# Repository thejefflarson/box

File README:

+-----------+
|           |
|   . . .   |
|   . . .   |
|   . . .   |
|           |
+-----------+

LED box for my son!

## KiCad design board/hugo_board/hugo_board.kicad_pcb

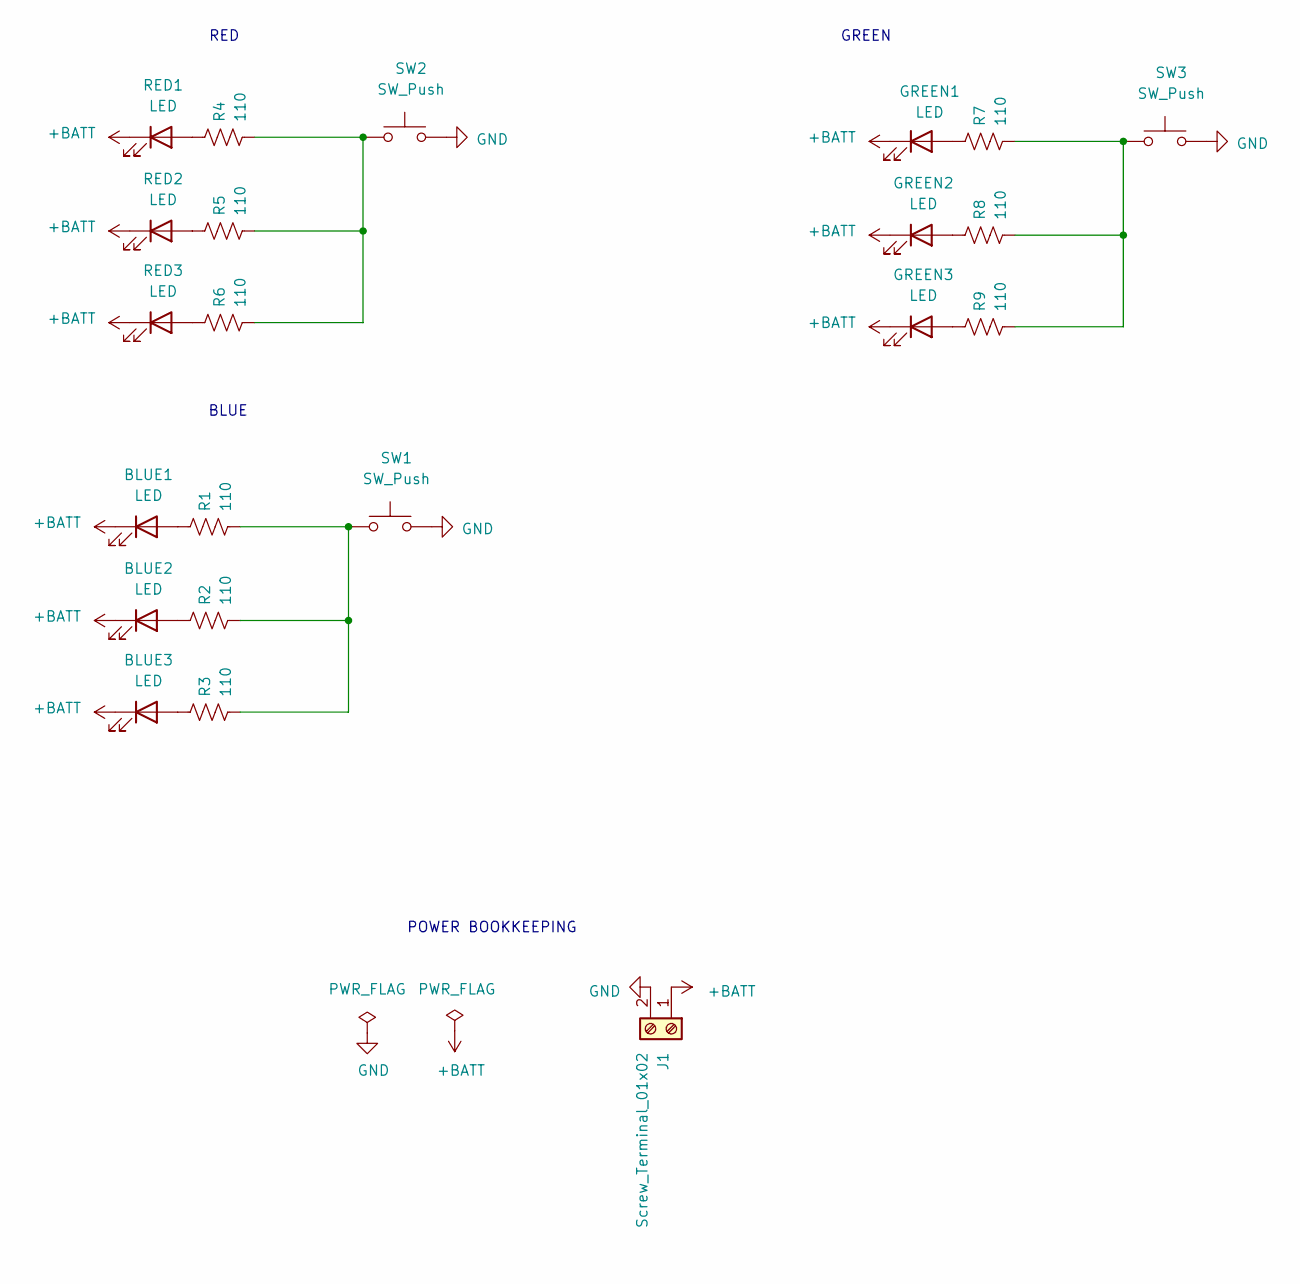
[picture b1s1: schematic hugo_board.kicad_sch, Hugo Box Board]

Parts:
BLUE1, BLUE2, BLUE3: LED; LED_D10.0mm
GREEN1, GREEN2, GREEN3: LED; LED_D10.0mm
J1: Screw_Terminal_01x02; JST_PH_S2B-PH-K_1x02_P2.00mm_Horizontal
R1, R2, R3, R4, R5, R6, R7, R8, R9: 110; R_Axial_DIN0204_L3.6mm_D1.6mm_P7.62mm_Horizontal
RED1, RED2, RED3: LED; LED_D10.0mm
SW1, SW2, SW3: SW_Push; TerminalBlock_4Ucon_1x02_P3.50mm_Horizontal

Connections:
+BATT: BLUE1.1 (K), BLUE2.1 (K), BLUE3.1 (K), GREEN1.1 (K), GREEN2.1 (K), GREEN3.1 (K), J1.1, RED1.1 (K), RED2.1 (K), RED3.1 (K)
GND: J1.2, SW1.2, SW2.2, SW3.2
unnamed: BLUE1.2 (A), R1.1
unnamed: BLUE2.2 (A), R2.1
unnamed: BLUE3.2 (A), R3.1
unnamed: GREEN1.2 (A), R7.1
unnamed: GREEN2.2 (A), R8.1
unnamed: GREEN3.2 (A), R9.1
unnamed: R1.2, R2.2, R3.2, SW1.1
unnamed: R4.1, RED1.2 (A)
unnamed: R4.2, R5.2, R6.2, SW2.1
unnamed: R5.1, RED2.2 (A)
unnamed: R6.1, RED3.2 (A)
unnamed: R7.2, R8.2, R9.2, SW3.1

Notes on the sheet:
RED
BLUE
POWER BOOKKEEPING
GREEN

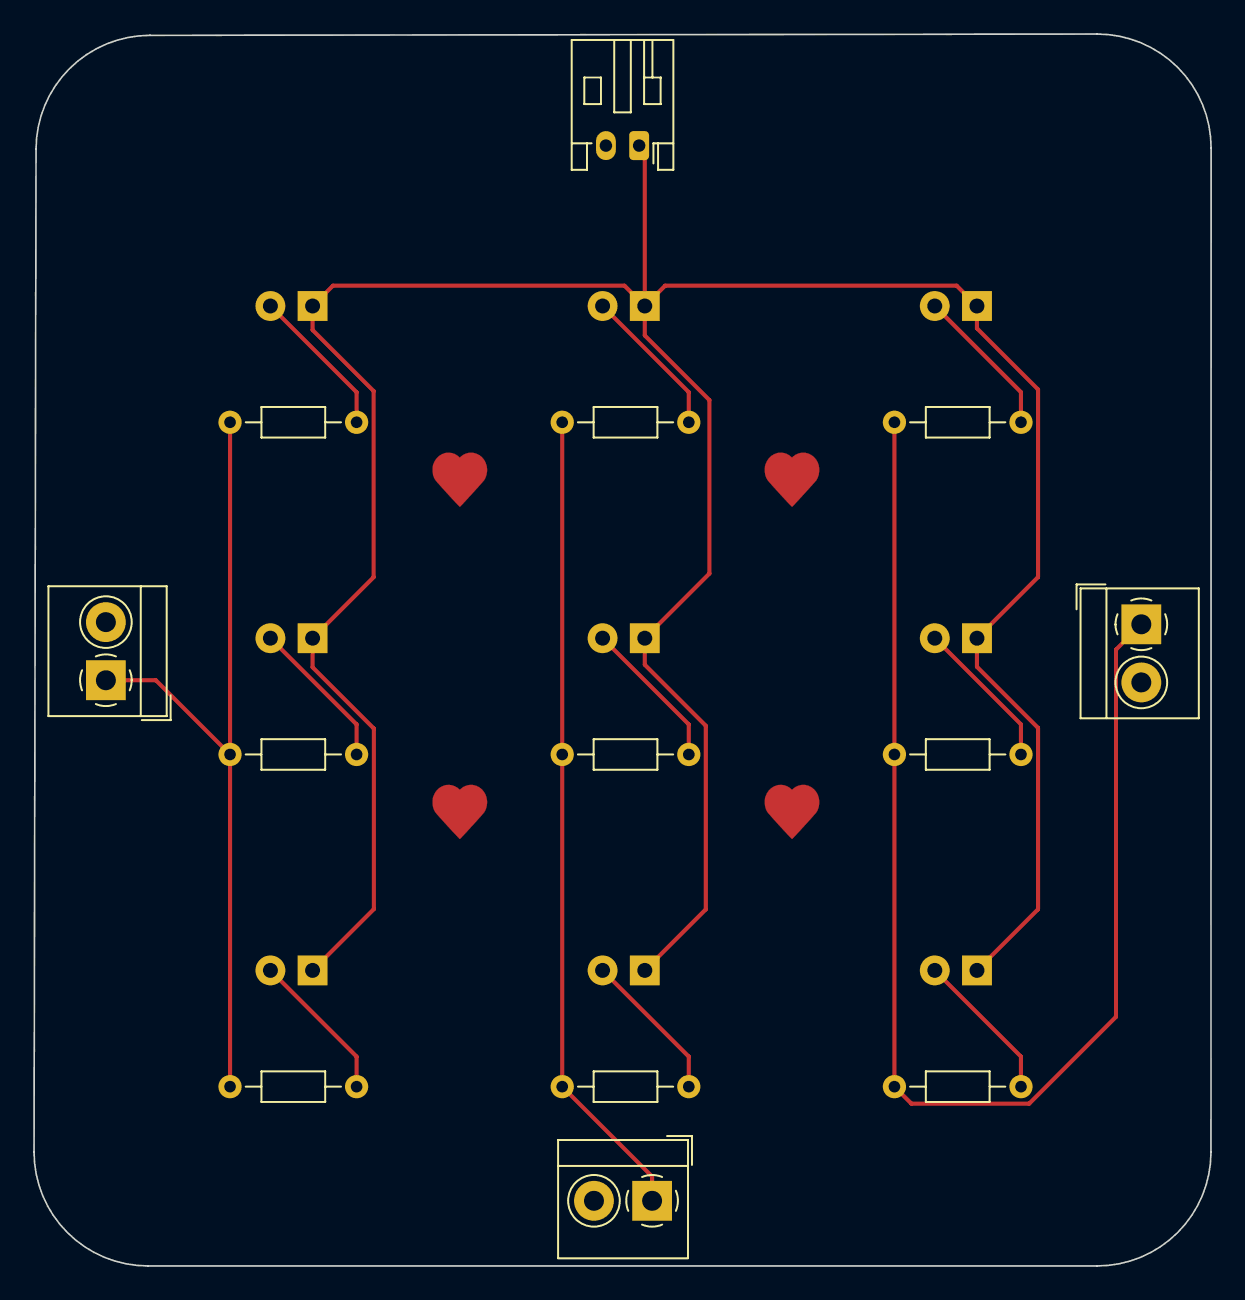
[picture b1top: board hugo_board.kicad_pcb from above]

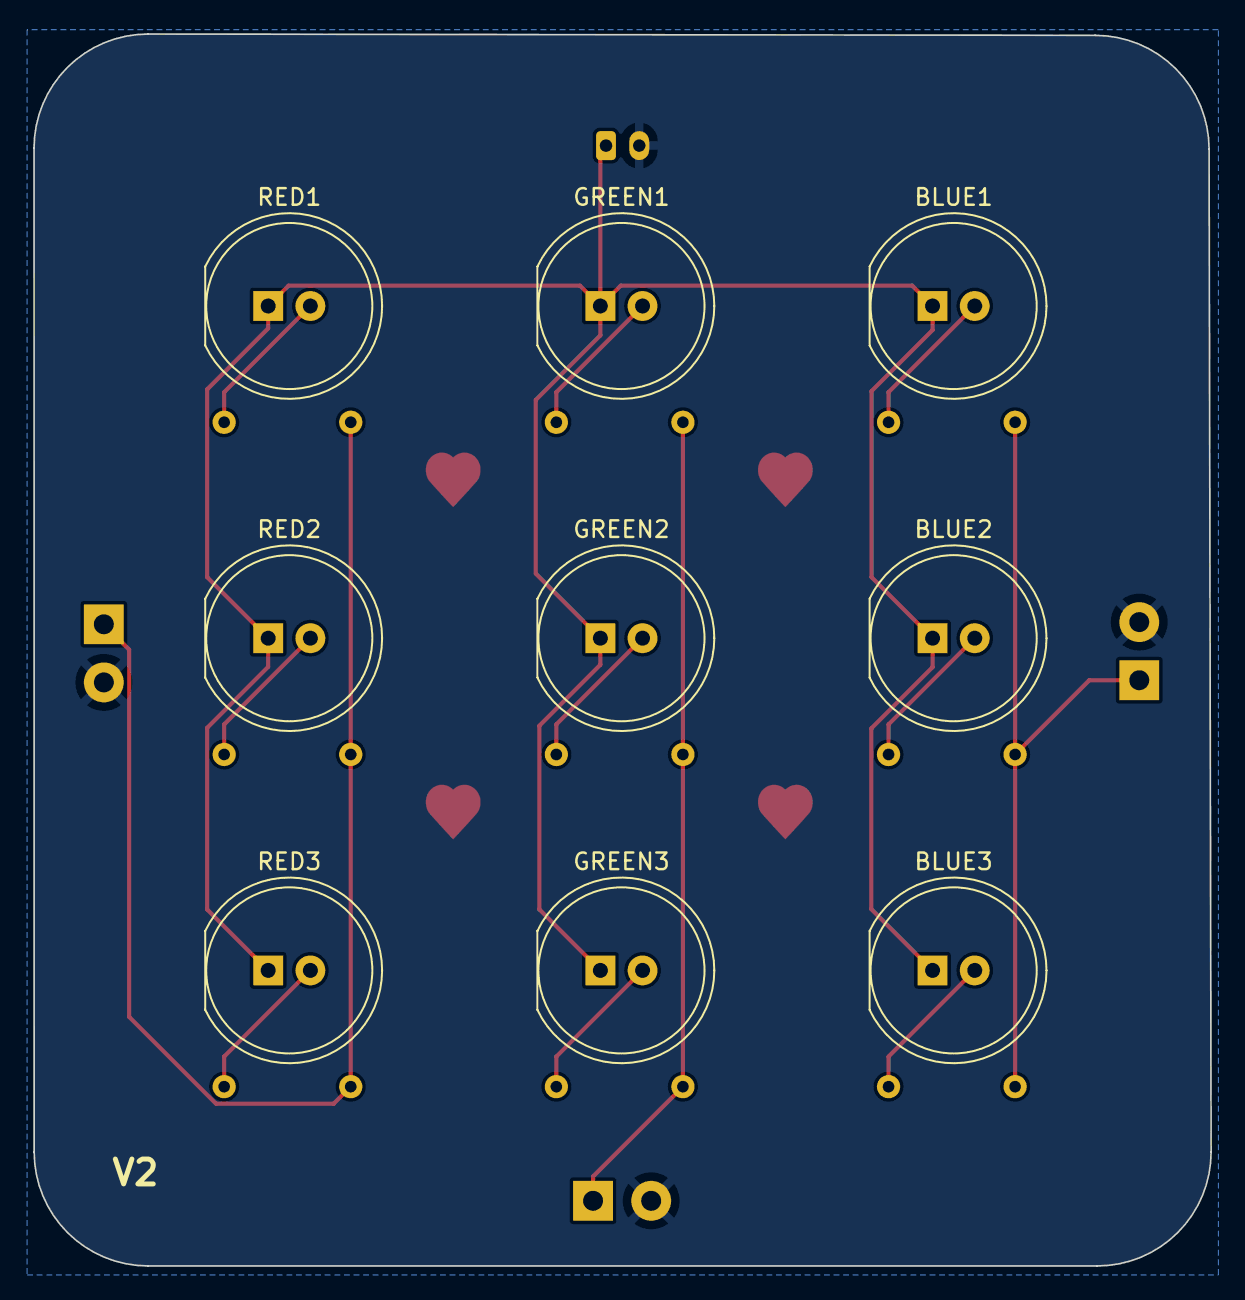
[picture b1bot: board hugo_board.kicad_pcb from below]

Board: 2 copper layers, 70.9 x 74.2 mm, 26 parts (9 on the bottom side), 14 nets.

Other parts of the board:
Ref**: Val**; drawing
Ref**#2, Ref**#3, Ref**#4: Val**; drawing

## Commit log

2021-05-12 version 2
